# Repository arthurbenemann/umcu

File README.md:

Small EVB for [TI mspm0c1104](https://www.ti.com/lit/ds/symlink/mspm0c1104.pdf)

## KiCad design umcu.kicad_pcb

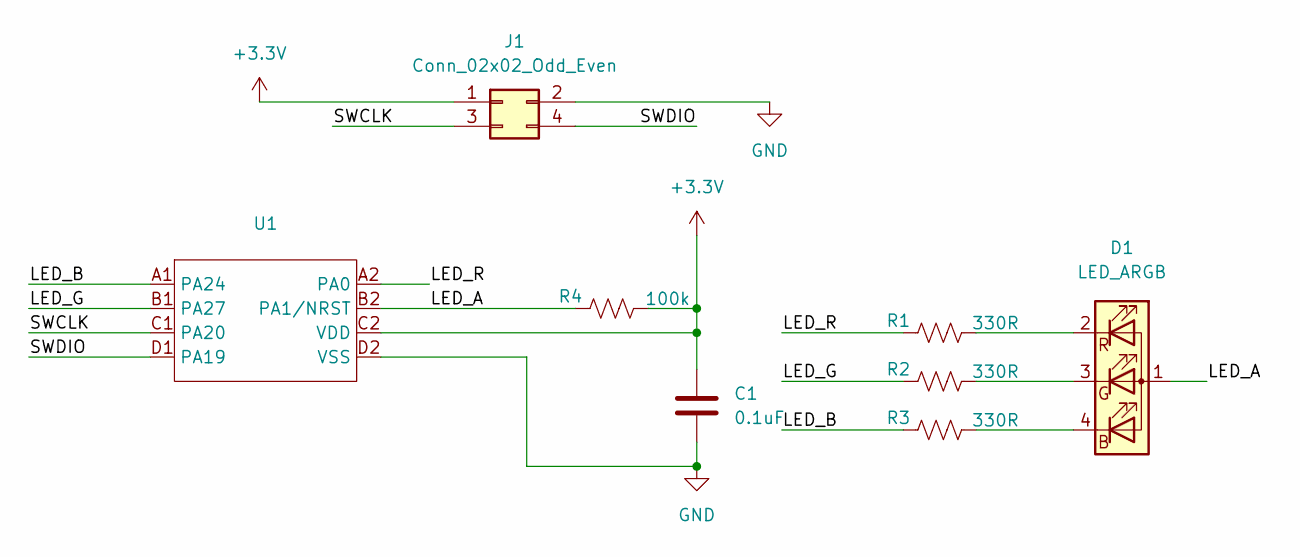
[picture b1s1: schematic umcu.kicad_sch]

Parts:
C1: 0.1uF; C_01005_0402Metric
D1: LED_ARGB; LED_Wurth_150044M155260
J1: Conn_02x02_Odd_Even; PinHeader_2x02_P2.54mm_Vertical
R1, R2, R3: 330R; R_01005_0402Metric
R4: 100k; R_01005_0402Metric
U1: BGA-8_2x4_0.86x1.6mm

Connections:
+3.3V: C1.1, J1.1, R4.2, U1.C2 (VDD)
/LED_A: D1.1 (A), R4.1, U1.B2 (PA1/NRST)
/LED_B: R3.1, U1.A1 (PA24)
/LED_G: R2.1, U1.B1 (PA27)
/LED_R: R1.1, U1.A2 (PA0)
/SWCLK: J1.3, U1.C1 (PA20)
/SWDIO: J1.4, U1.D1 (PA19)
GND: C1.2, J1.2, U1.D2 (VSS)
unnamed: D1.4 (BK), R3.2
unnamed: D1.3 (GK), R2.2
unnamed: D1.2 (RK), R1.2

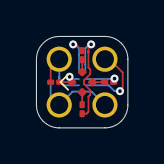
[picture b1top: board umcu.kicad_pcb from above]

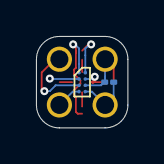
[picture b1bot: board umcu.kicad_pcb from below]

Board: 2 copper layers, 5.1 x 5.1 mm, 8 parts (3 on the bottom side), 11 nets.

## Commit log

2025-03-15 add gitignore
2025-03-16 clean-up silkscreen
2025-03-16 switch design to 2L board
